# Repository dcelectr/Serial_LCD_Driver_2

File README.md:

# Serial_LCD_Driver_2
LCD Screen Driver with 74HC595 (for LCDs with 2x8 header).
This uses the 74HC595 to drive LCD displays such as 1602, 1604, 2002, or 2004 with 5V, GND and three Arduino pins (DIN, CS, and CLK). Compatible with screens that have 2x8 male header.
It is recommended to use a 2x8 male header on the LCD and 1x8 female socket on the Serial_LCD_Driver_2.
Note that in the KiCad files male header is used (although the 3D .png rendering shows how the female socket should be populated), because I wanted to have pin for pin maping (ignore the 3D rendering in the KiCad files).
The LED (D1) and R2 are optional. You can populate for diagnostics (test the hardware), or connect a panel LED with wires to the Serial_LCD_Driver_2.
It is recommended to use a resistance value for R2 no lower than 470 Ohms (preferably use 1K with high efficiency LEDs).
The Q1 is used to provide current for the LCD back-light, so that the 74HC595 does not bear the burden to provide the required back-light current (some LCD back-lights draw as much as 200mA). The R1 can be adjusted (1K to 10K) to achieve Q1 saturation for or reduce the current to a desired brightness.
This design has been built and tested with the code provided in the Serial_LCD_Driver repository. It works!

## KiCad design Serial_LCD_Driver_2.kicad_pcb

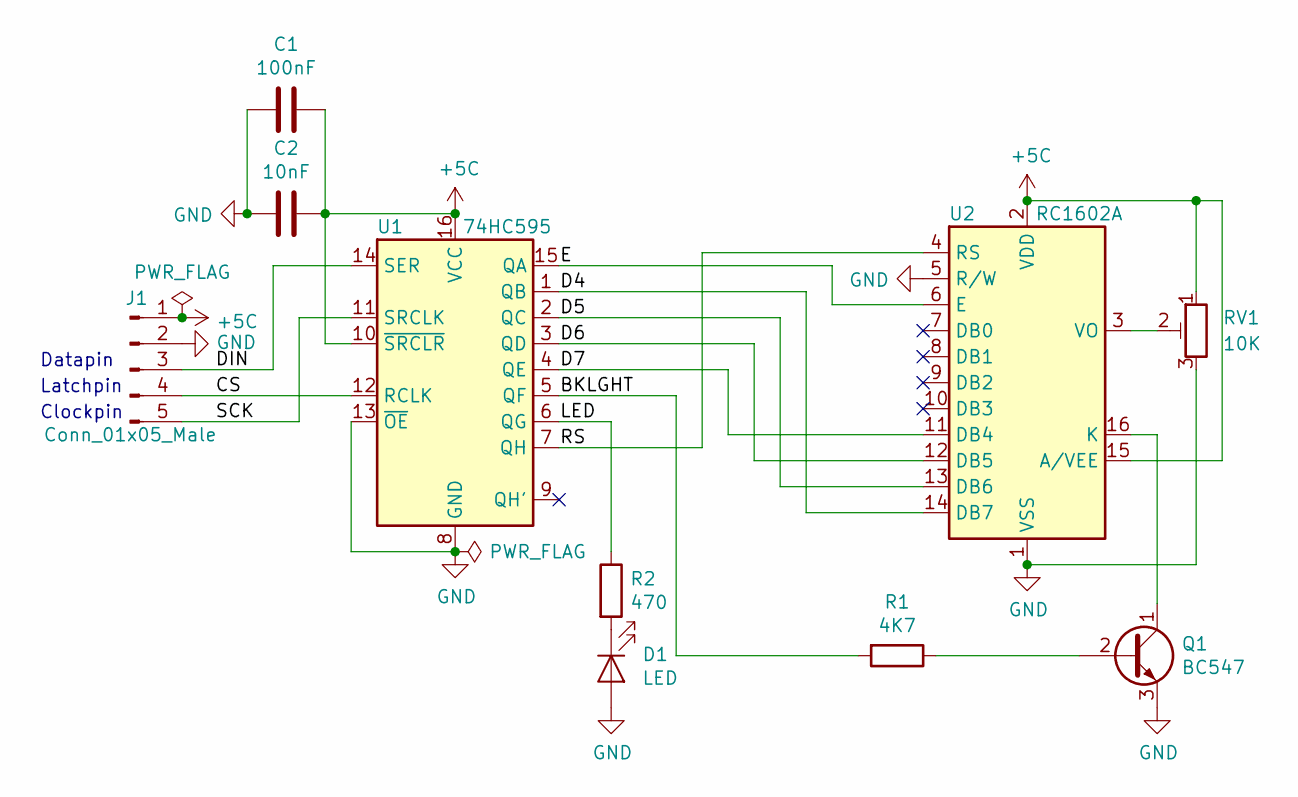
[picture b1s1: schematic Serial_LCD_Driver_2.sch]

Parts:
C1: 100nF; C_Disc_D3.0mm_W1.6mm_P2.50mm
C2: 10nF; C_Disc_D3.0mm_W1.6mm_P2.50mm
D1: LED; LED_D3.0mm
J1: Conn_01x05_Male; PinHeader_1x05_P2.54mm_Vertical
Q1: BC547; TO-92_Inline_Wide
R1: 4K7; R_Axial_DIN0204_L3.6mm_D1.6mm_P7.62mm_Horizontal
R2: 470; R_Axial_DIN0204_L3.6mm_D1.6mm_P7.62mm_Horizontal
RV1: 10K; Potentiometer_Bourns_3009P_Horizontal
U1: 74HC595; DIP-16_W7.62mm_LongPads
U2: RC1602A; PinHeader_2x08_P2.54mm_Vertical

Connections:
+5C: C1.1, C2.1, J1.1, RV1.1, U1.10 (~SRCLR), U1.16 (VCC), U2.2 (VDD), U2.15 (A/VEE)
/BKLGHT: R1.2, U1.5 (QF)
/CS: J1.4, U1.12 (RCLK)
/D4: U1.1 (QB), U2.14 (DB7)
/D5: U1.2 (QC), U2.13 (DB6)
/D6: U1.3 (QD), U2.12 (DB5)
/D7: U1.4 (QE), U2.11 (DB4)
/DIN: J1.3, U1.14 (SER)
/E: U1.15 (QA), U2.6 (E)
/LED: R2.1, U1.6 (QG)
/RS: U1.7 (QH), U2.4 (RS)
/SCK: J1.5, U1.11 (SRCLK)
GND: C1.2, C2.2, D1.2 (A), J1.2, Q1.3 (E), RV1.3, U1.8 (GND), U1.13 (~OE), U2.1 (VSS), U2.5 (R/W)
unnamed: D1.1 (K), R2.2
unnamed: Q1.1 (C), U2.16 (K)
unnamed: Q1.2 (B), R1.1
unnamed: RV1.2, U2.3 (VO)

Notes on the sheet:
Datapin
Latchpin
Clockpin

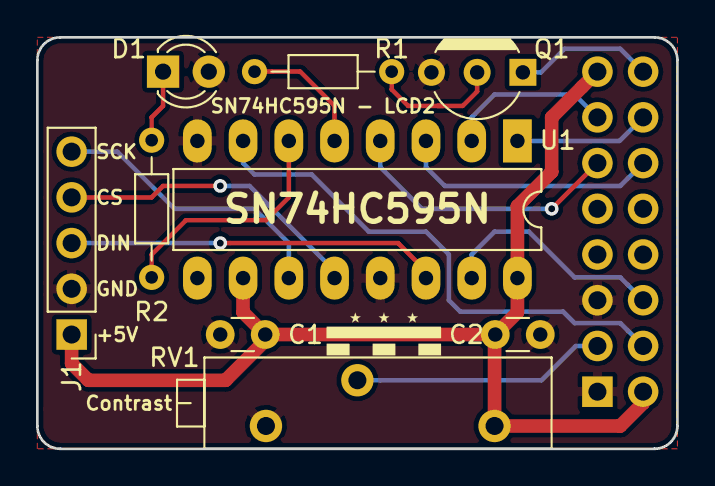
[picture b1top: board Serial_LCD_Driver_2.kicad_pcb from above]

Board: 2 copper layers, 35.6 x 22.9 mm, 10 parts (1 on the bottom side), 17 nets.

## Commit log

2019-07-24 KiCad Files
2019-07-24 3D Renderings
2020-12-17 Added Bill of Materials CSV file
